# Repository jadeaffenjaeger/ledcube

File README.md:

# Contents
Codebase and Schematics for an easily extendable LED cube based on the STM32F103 and TPIC6B595 shift registers.

## Structure
The cube uses two types of driver PCBs: One *Level driver*, which activates the anodes for one out of eight levels at a time. The PCB also contains the main MCU on a "Blue Pill" breakout board, as well as voltage regulation for the MCU and 74HCT245 bus driver for 3.3V-5V level conversion.
Four *Row Drivers*, each of which controls the anodes of 16 of 64 columns independently.
All boards are designed to be chained together with the level driver coming first, followed by the row drivers.
This makes it possible to control the cube with just 3 pins on the MCU. All boards are designed to be extendable and reusable for cubes that require more or less contol pins

## Row Driver Boards
The driver board contains two TPIC6B595, capable of controlling a total of 16 outputs with a current sinking capability of 100mA per channel, eliminating the need for external driving transistors. Resistors can be replaced easily to allow for different types of LEDs. The boards are designed to be daisy-chained together, so that larger cubes can be built without redesigning anything, just by adding more driver boards. Also, this easily fills up the minimum order with most board houses. I had mine
manufactured at [Dirty PCBs](www.dirtypcbs.com), where 10 boards cost around 15USD.

Inputs on the board are:

    1 VCC
    2 Serial Clock
    3 Register Clock/Latch
    4 Serial Data
    5 GND

Assembled Board:

## Level Driver board
In an earlier iteration, this was a very simple board that only contained the shift register IC and the p-channel MOSFETs. As of now, the board was redesigned to contain the MCU, voltage regulation and the shift register and MOS transistors

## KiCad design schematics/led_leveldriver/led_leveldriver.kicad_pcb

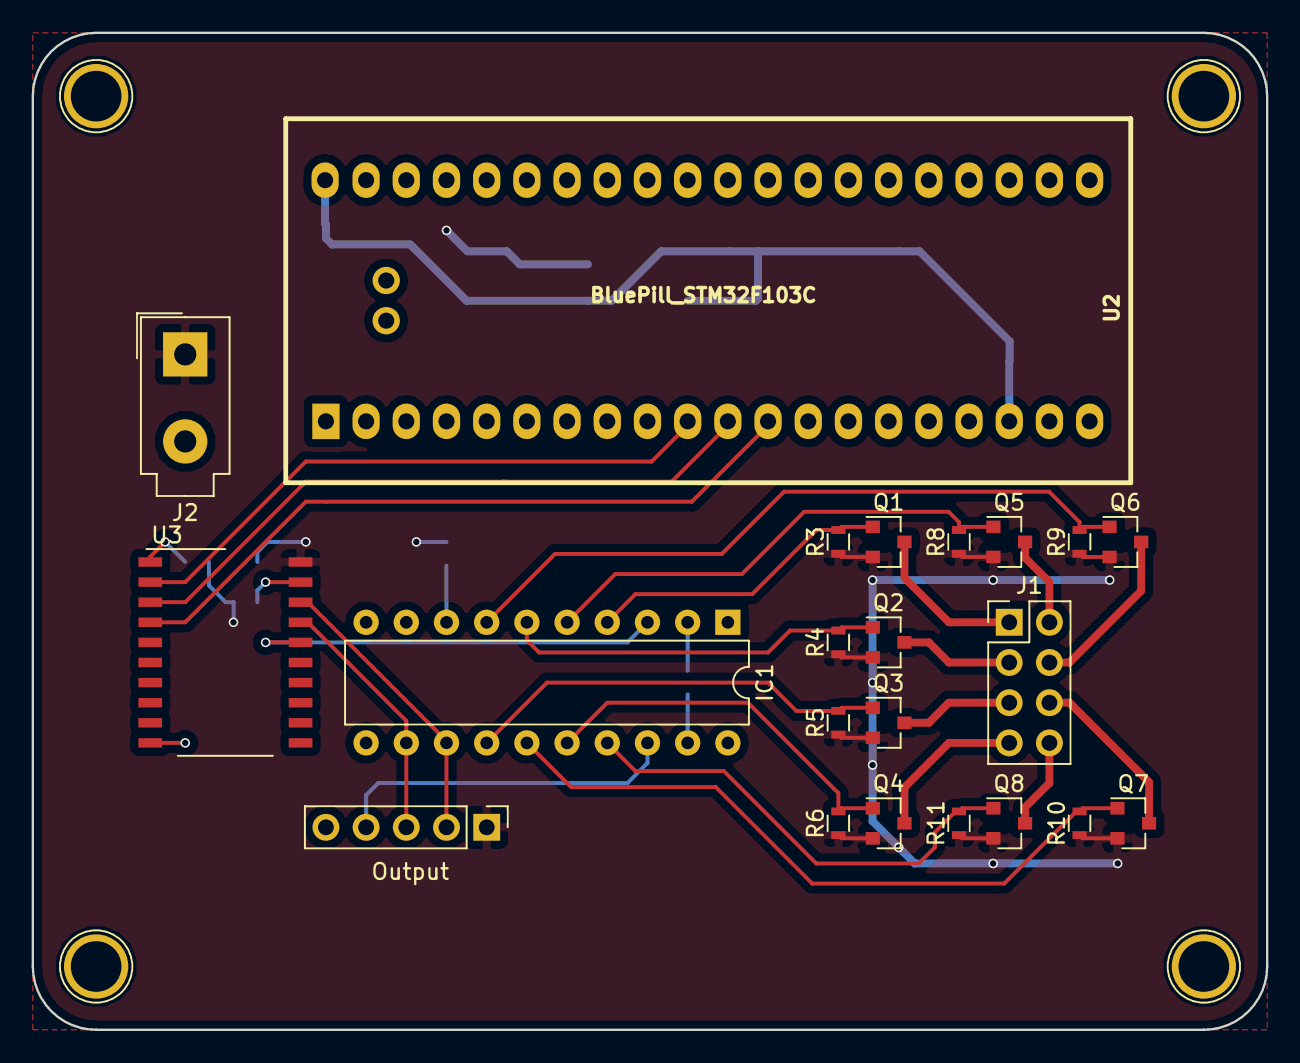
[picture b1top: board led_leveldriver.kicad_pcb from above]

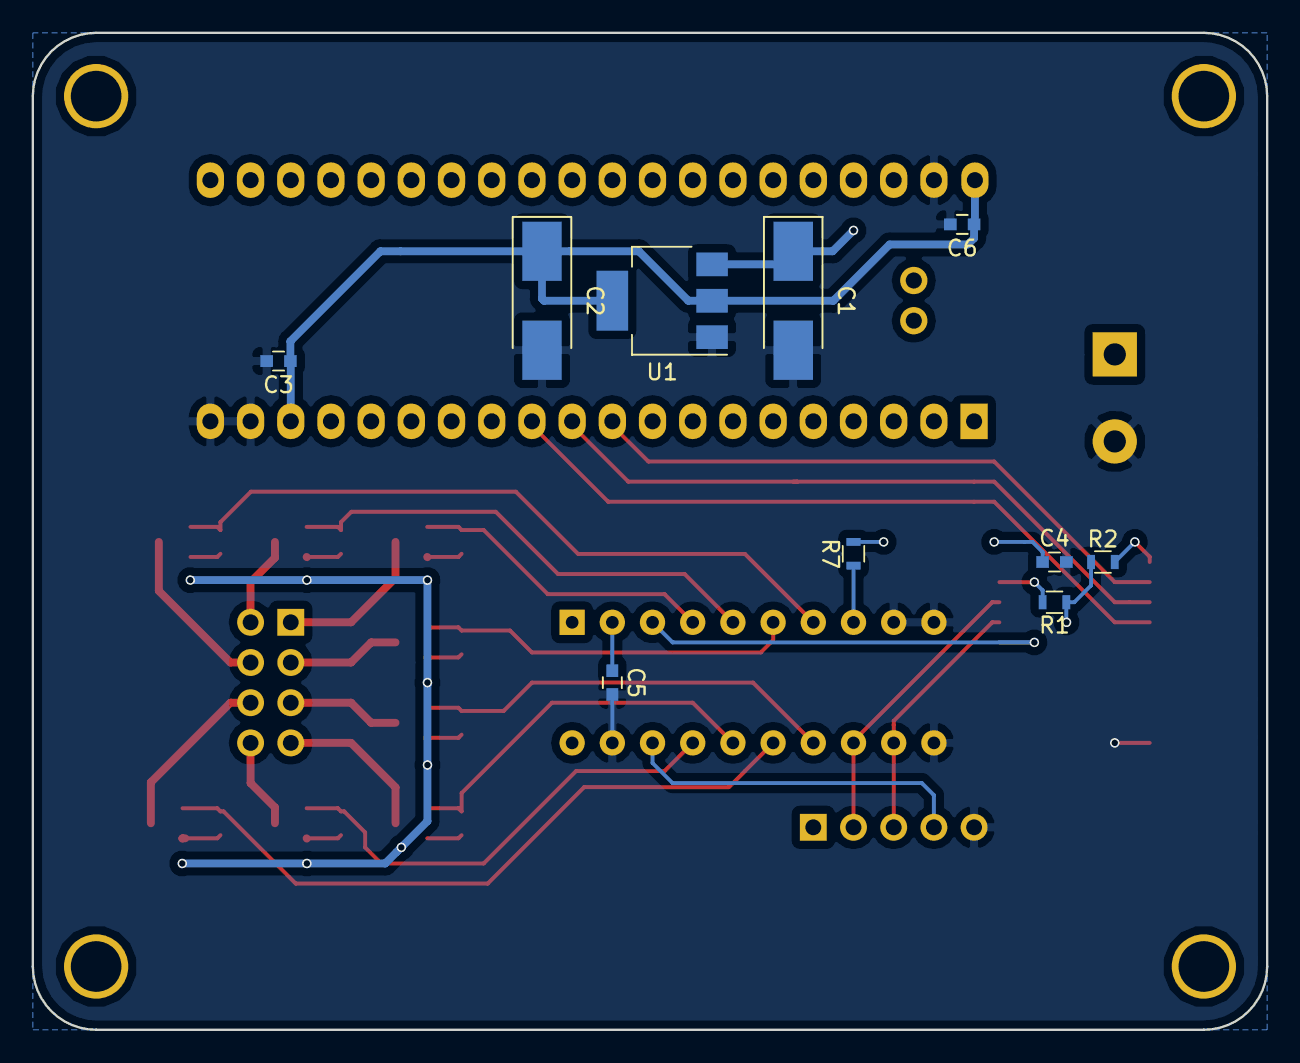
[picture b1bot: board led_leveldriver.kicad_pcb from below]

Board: 2 copper layers, 78.0 x 63.0 mm, 32 parts (10 on the bottom side), 29 nets.

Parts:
C1, C2: 10u; CP_Tantalum_Case-U_EIA-6032-15_Hand
C3, C4, C5, C6: 0.1uF; C_0603
IC1: TPIC6B595; DIP-20_W7.62mm
J1: Conn_02x04_Odd_Even; Pin_Header_Straight_2x04_Pitch2.54mm
J2: 5V_IN; Molex_MiniFit-JR-5556-02A_2x01x4.20mm_Straight
Output: CONN_01X05; Pin_Header_Straight_1x05_Pitch2.54mm
Q1, Q2, Q3, Q4, Q5, Q6, Q7, Q8: Q_PMOS_GSD; SOT-23
R1, R2, R3, R4, R5, R6, R7, R8, R9, R10, R11: 10k; R_0603
U1: LM1117-3.3; SOT-223-3_TabPin2
U2: BluePill_STM32F103C
U3: 74HCT245; SO-20_12.8x7.5mm_Pitch1.27mm

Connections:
+3V3: C2.1, C3.1, C6.1, U1.2, U2.18, U2.40
/DATA: IC1.3, U3.16
/DOUT: IC1.18, Output.4
/L0: IC1.4, Q1.1, R3.2
/L1: IC1.5, Q5.1, R8.2
/L2: IC1.6, Q2.1, R4.2
/L3: IC1.7, Q6.1, R9.2
/L4: IC1.14, Q3.1, R5.2
/L5: IC1.15, Q7.1, R10.2
/L6: IC1.16, Q4.1, R6.2
/L7: IC1.17, Q8.1, R11.2
/RCK: IC1.12, Output.3, U3.17
/SRCK: IC1.13, Output.2, U3.18
GND: C1.2, C2.2, C3.2, C4.2, C5.2, C6.2, IC1.9, IC1.10, IC1.11, IC1.19, J2.2, Output.5, U1.1, U2.19, U2.20, U2.39, U3.10
unnamed: IC1.8, R7.1
unnamed: J1.1, Q1.3
unnamed: J1.2, Q5.3
unnamed: J1.3, Q2.3
unnamed: J1.4, Q6.3
unnamed: J1.5, Q3.3
unnamed: J1.6, Q7.3
unnamed: J1.7, Q4.3
unnamed: J1.8, Q8.3
unnamed: R1.2, U3.19
unnamed: R2.2, U3.1
unnamed: U2.10, U3.2
unnamed: U2.11, U3.3
unnamed: U2.12, U3.4
VCC: C1.1, C4.1, C5.1, IC1.2, J2.1, Output.1, Q1.2, Q2.2, Q3.2, Q4.2, Q5.2, Q6.2, Q7.2, Q8.2, R1.1, R2.1, R3.1, R4.1, R5.1, R6.1, R7.2, R8.1, R9.1, R10.1, R11.1, U1.3, U3.20

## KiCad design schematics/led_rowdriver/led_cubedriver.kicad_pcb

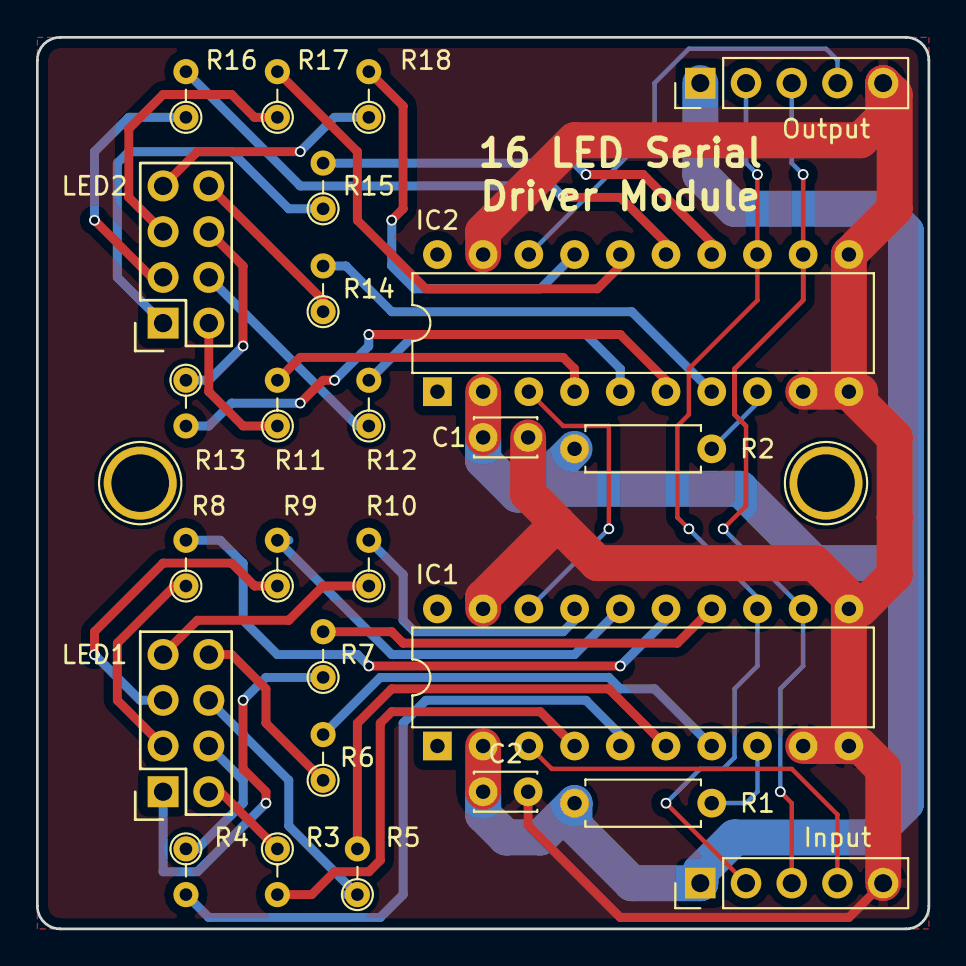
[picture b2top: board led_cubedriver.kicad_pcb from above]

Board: 2 copper layers, 49.5 x 49.5 mm, 26 parts (0 on the bottom side), 41 nets.

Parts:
C1, C2: 0.1uF; C_Disc_D3.4mm_W2.1mm_P2.50mm
IC1, IC2: TPIC6B595; DIP-20_W7.62mm
Input: CONN_01X05; Pin_Header_Straight_1x05_Pitch2.54mm
LED1, LED2: CONN_02X04; Socket_Strip_Straight_2x04
Output: CONN_01X05; Pin_Header_Straight_1x05_Pitch2.54mm
R1, R2: 10k; R_Axial_DIN0207_L6.3mm_D2.5mm_P7.62mm_Horizontal
R3, R4, R5, R6, R7, R8, R9, R10, R11, R12, R13, R14, R15, R16, R17, R18: 100; R_Axial_DIN0204_L3.6mm_D1.6mm_P2.54mm_Vertical

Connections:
/RCK: IC1.12, IC2.12, Input.3, Output.3
/SRCK: IC1.13, IC2.13, Input.2, Output.2
GND: C1.2, C2.2, IC1.9, IC1.10, IC1.11, IC1.19, IC2.9, IC2.10, IC2.11, IC2.19, Input.5, Output.5
unnamed: IC1.3, Input.4
unnamed: IC2.18, Output.4
unnamed: IC1.4, R3.2
unnamed: IC1.5, R4.2
unnamed: IC1.6, R5.2
unnamed: IC1.7, R6.2
unnamed: IC1.8, R1.1
unnamed: IC1.14, R7.2
unnamed: IC1.15, R8.2
unnamed: IC1.16, R9.2
unnamed: IC1.17, R10.2
unnamed: IC1.18, IC2.3
unnamed: IC2.4, R11.2
unnamed: IC2.5, R12.2
unnamed: IC2.6, R13.2
unnamed: IC2.7, R14.2
unnamed: IC2.8, R2.1
unnamed: IC2.14, R15.2
unnamed: IC2.15, R16.2
unnamed: IC2.16, R17.2
unnamed: IC2.17, R18.2
unnamed: LED1.1, R7.1
unnamed: LED1.2, R3.1
unnamed: LED1.3, R8.1
unnamed: LED1.4, R4.1
unnamed: LED1.5, R9.1
unnamed: LED1.6, R5.1
unnamed: LED1.7, R10.1
unnamed: LED1.8, R6.1
unnamed: LED2.1, R15.1
unnamed: LED2.2, R11.1
unnamed: LED2.3, R16.1
unnamed: LED2.4, R12.1
unnamed: LED2.5, R17.1
unnamed: LED2.6, R13.1
unnamed: LED2.7, R18.1
unnamed: LED2.8, R14.1
VCC: C1.1, C2.1, IC1.2, IC2.2, Input.1, Output.1, R1.2, R2.2

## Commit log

2017-03-12 Add board schematics and readme
2017-03-18 Add board interface description to README
2017-03-18 Fix Markdown formatting
2017-03-18 Add Board picture and data sheet
2017-03-19 Add CubeMX configuration
2017-06-30 Add initial firmware
2017-06-30 remove CubeMX template
2017-06-30 blinky pattern
2018-05-09 Add PCB layout for level driver
2018-05-09 Add gitignore
2018-06-15 Change project file structure
2018-06-15 Untested Pixel extrapolation
2018-06-15 Fix error in point extrapolation
2018-06-15 Add Flash target to Makefile
2018-06-27 Add simple LFSR and animations file
2018-07-01 Add Sine LUT and drop animation
2018-07-03 Fix off-by-one error in sinus table
2018-07-04 Add Falling Grid animation and file header comments
2018-07-28 Restructure Schematics folder
2018-07-28 Add Library files to repository
2018-07-29 Rework Level driver to STM32 breakout board
2018-07-29 Update readme with new design
2018-07-29 Add animations
2018-08-09 Remove BAM brightness control
2018-09-30 Fix compiler warnings
2018-09-30 Add animation descriptions
2018-09-30 Add comments to LFSR implementation
